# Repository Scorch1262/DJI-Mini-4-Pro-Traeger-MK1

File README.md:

# DJI-Mini-4-Pro-Tr-ger-MK1

Achtung:

Der Lidar-Sensor unter der Drohne muss abgeklebt werden !!!

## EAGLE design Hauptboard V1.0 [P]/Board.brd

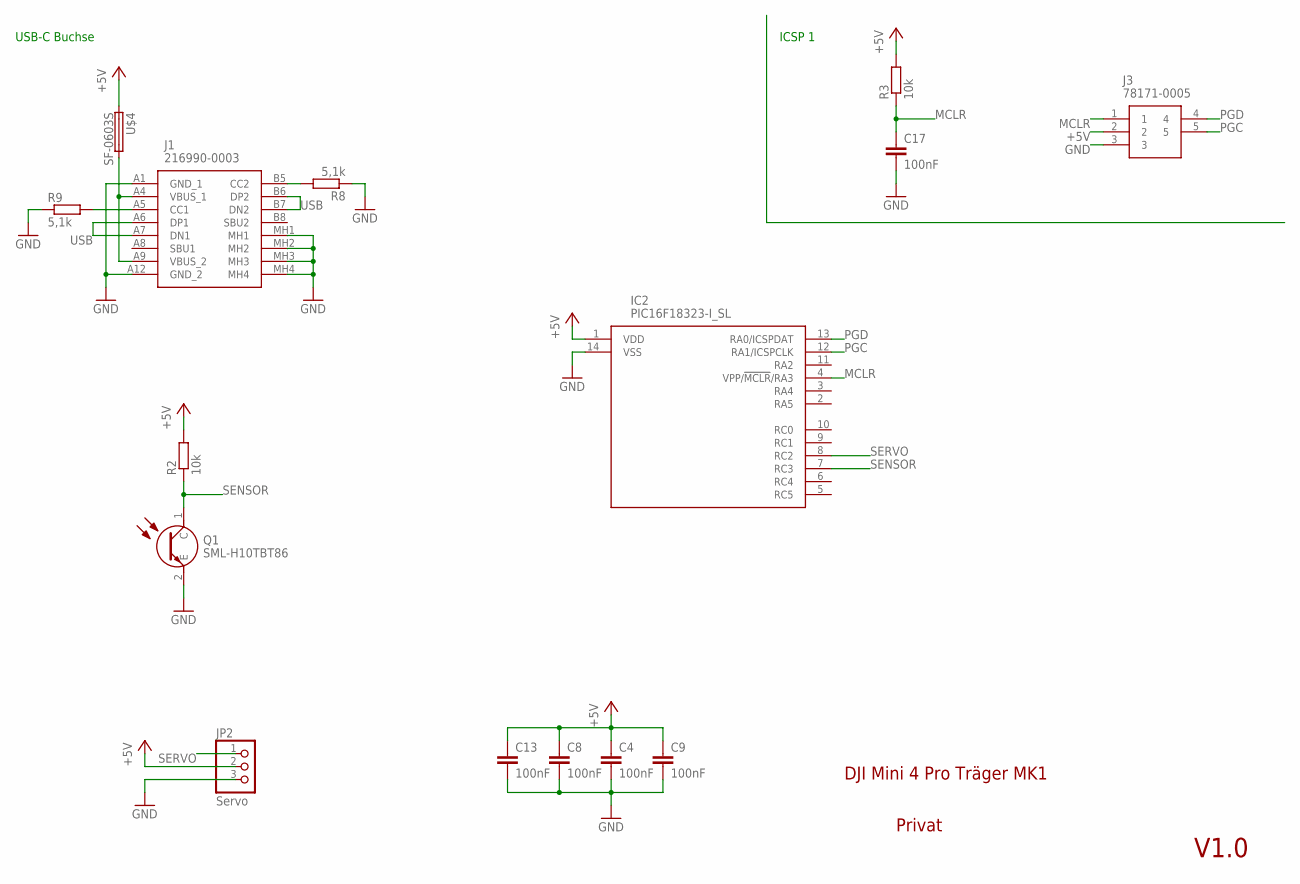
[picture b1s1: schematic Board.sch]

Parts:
C4, C8, C9, C13, C17: 100nF; C0805
IC2: PIC16F18323-I_SL; SOIC127P600X175-14N
J1: 216990-0003; 2169900003
J3: 78171-0005
JP2: Servo; 1X03/90
Q1: SML-H10TBT86; SMLH10TBT86
R2, R3: 10k; R0805
R8, R9: 5,1k; R0805
U$4: SF-0603S; R0603

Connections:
+5V: C4.1, C8.1, C9.1, C13.1, IC2.1 (VDD), J3.2, JP2.2, R2.2, R3.2, U$4.1
GND: C4.2, C8.2, C9.2, C13.2, C17.2, IC2.14 (VSS), J1.A1 (GND_1), J1.A12 (GND_2), J1.MH1, J1.MH2, J1.MH3, J1.MH4, J3.3, JP2.3, Q1.2 (E), R8.1, R9.1
MCLR: C17.1, IC2.4 (VPP/!MCLR!/RA3), J3.1, R3.1
unnamed: J1.A4 (VBUS_1), J1.A9 (VBUS_2), U$4.2
unnamed: J1.A5 (CC1), R9.2
unnamed: J1.B5 (CC2), R8.2
PGC: IC2.12 (RA1/ICSPCLK), J3.5
PGD: IC2.13 (RA0/ICSPDAT), J3.4
SENSOR: IC2.7 (RC3), Q1.1 (C), R2.1
SERVO: IC2.8 (RC2), JP2.1
USB: J1.A6 (DP1), J1.A7 (DN1), J1.B6 (DP2), J1.B7 (DN2)

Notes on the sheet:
DJI Mini 4 Pro Träger MK1
Privat
V1.0
USB-C Buchse
ICSP 1

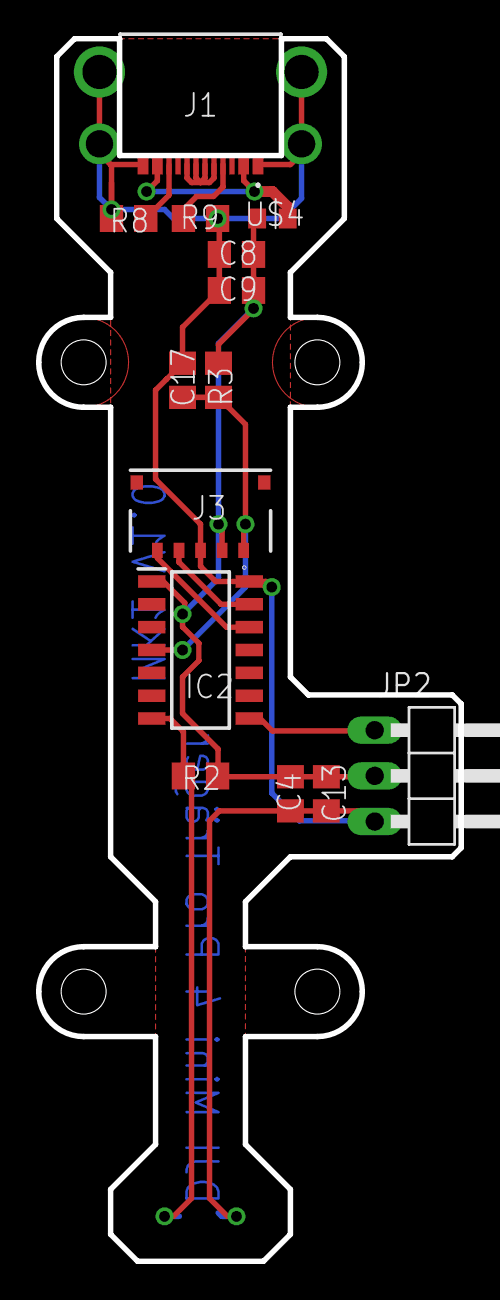
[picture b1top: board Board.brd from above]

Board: 2 copper layers, 23.5 x 68.0 mm, 15 parts (1 on the bottom side), 11 nets.

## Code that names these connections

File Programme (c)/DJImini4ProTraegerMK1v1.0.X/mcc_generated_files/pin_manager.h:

/**
  @Generated Pin Manager Header File

  @Company:
    Microchip Technology Inc.

  @File Name:
    pin_manager.h

  @Summary:
    This is the Pin Manager file generated using PIC10 / PIC12 / PIC16 / PIC18 MCUs

  @Description
    This header file provides APIs for driver for .
    Generation Information :
        Product Revision  :  PIC10 / PIC12 / PIC16 / PIC18 MCUs - 1.81.7
        Device            :  PIC16F18323
        Driver Version    :  2.11
    The generated drivers are tested against the following:
        Compiler          :  XC8 2.31 and above
        MPLAB 	          :  MPLAB X 5.45	
*/

/*
    (c) 2018 Microchip Technology Inc. and its subsidiaries. 
    
    Subject to your compliance with these terms, you may use Microchip software and any 
    derivatives exclusively with Microchip products. It is your responsibility to comply with third party 
    license terms applicable to your use of third party software (including open source software) that 
    may accompany Microchip software.
    
    THIS SOFTWARE IS SUPPLIED BY MICROCHIP "AS IS". NO WARRANTIES, WHETHER 
    EXPRESS, IMPLIED OR STATUTORY, APPLY TO THIS SOFTWARE, INCLUDING ANY 
    IMPLIED WARRANTIES OF NON-INFRINGEMENT, MERCHANTABILITY, AND FITNESS 
    FOR A PARTICULAR PURPOSE.
    
    IN NO EVENT WILL MICROCHIP BE LIABLE FOR ANY INDIRECT, SPECIAL, PUNITIVE, 
    INCIDENTAL OR CONSEQUENTIAL LOSS, DAMAGE, COST OR EXPENSE OF ANY KIND 
    WHATSOEVER RELATED TO THE SOFTWARE, HOWEVER CAUSED, EVEN IF MICROCHIP 
    HAS BEEN ADVISED OF THE POSSIBILITY OR THE DAMAGES ARE FORESEEABLE. TO 
    THE FULLEST EXTENT ALLOWED BY LAW, MICROCHIP'S TOTAL LIABILITY ON ALL 
    CLAIMS IN ANY WAY RELATED TO THIS SOFTWARE WILL NOT EXCEED THE AMOUNT 
    OF FEES, IF ANY, THAT YOU HAVE PAID DIRECTLY TO MICROCHIP FOR THIS 
    SOFTWARE.
*/

#ifndef PIN_MANAGER_H
#define PIN_MANAGER_H

/**
  Section: Included Files
*/

#include <xc.h>

#define INPUT   1
#define OUTPUT  0

#define HIGH    1
#define LOW     0

#define ANALOG      1
#define DIGITAL     0

#define PULL_UP_ENABLED      1
#define PULL_UP_DISABLED     0

// get/set Servo aliases
#define Servo_TRIS                 TRISCbits.TRISC2
#define Servo_LAT                  LATCbits.LATC2
#define Servo_PORT                 PORTCbits.RC2
#define Servo_WPU                  WPUCbits.WPUC2
#define Servo_OD                   ODCONCbits.ODCC2
#define Servo_ANS                  ANSELCbits.ANSC2
#define Servo_SetHigh()            do { LATCbits.LATC2 = 1; } while(0)
#define Servo_SetLow()             do { LATCbits.LATC2 = 0; } while(0)
#define Servo_Toggle()             do { LATCbits.LATC2 = ~LATCbits.LATC2; } while(0)
#define Servo_GetValue()           PORTCbits.RC2
#define Servo_SetDigitalInput()    do { TRISCbits.TRISC2 = 1; } while(0)
#define Servo_SetDigitalOutput()   do { TRISCbits.TRISC2 = 0; } while(0)
#define Servo_SetPullup()          do { WPUCbits.WPUC2 = 1; } while(0)
#define Servo_ResetPullup()        do { WPUCbits.WPUC2 = 0; } while(0)
#define Servo_SetPushPull()        do { ODCONCbits.ODCC2 = 0; } while(0)
#define Servo_SetOpenDrain()       do { ODCONCbits.ODCC2 = 1; } while(0)
#define Servo_SetAnalogMode()      do { ANSELCbits.ANSC2 = 1; } while(0)
#define Servo_SetDigitalMode()     do { ANSELCbits.ANSC2 = 0; } while(0)

// get/set Sensor aliases
#define Sensor_TRIS                 TRISCbits.TRISC3
#define Sensor_LAT                  LATCbits.LATC3
#define Sensor_PORT                 PORTCbits.RC3
#define Sensor_WPU                  WPUCbits.WPUC3
#define Sensor_OD                   ODCONCbits.ODCC3
#define Sensor_ANS                  ANSELCbits.ANSC3
#define Sensor_SetHigh()            do { LATCbits.LATC3 = 1; } while(0)
#define Sensor_SetLow()             do { LATCbits.LATC3 = 0; } while(0)
#define Sensor_Toggle()             do { LATCbits.LATC3 = ~LATCbits.LATC3; } while(0)
#define Sensor_GetValue()           PORTCbits.RC3
#define Sensor_SetDigitalInput()    do { TRISCbits.TRISC3 = 1; } while(0)
#define Sensor_SetDigitalOutput()   do { TRISCbits.TRISC3 = 0; } while(0)
#define Sensor_SetPullup()          do { WPUCbits.WPUC3 = 1; } while(0)
#define Sensor_ResetPullup()        do { WPUCbits.WPUC3 = 0; } while(0)
#define Sensor_SetPushPull()        do { ODCONCbits.ODCC3 = 0; } while(0)
#define Sensor_SetOpenDrain()       do { ODCONCbits.ODCC3 = 1; } while(0)
#define Sensor_SetAnalogMode()      do { ANSELCbits.ANSC3 = 1; } while(0)
#define Sensor_SetDigitalMode()     do { ANSELCbits.ANSC3 = 0; } while(0)

/**
   @Param
    none
   @Returns
    none
   @Description
    GPIO and peripheral I/O initialization
   @Example
    PIN_MANAGER_Initialize();
 */
void PIN_MANAGER_Initialize (void);

/**
 * @Param
    none
 * @Returns
    none
 * @Description
    Interrupt on Change Handling routine
 * @Example
    PIN_MANAGER_IOC();
 */
void PIN_MANAGER_IOC(void);



#endif // PIN_MANAGER_H
/**
 End of File
*/

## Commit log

2025-03-29 initalisierung
2025-04-12 Projekt abgeschlossen
